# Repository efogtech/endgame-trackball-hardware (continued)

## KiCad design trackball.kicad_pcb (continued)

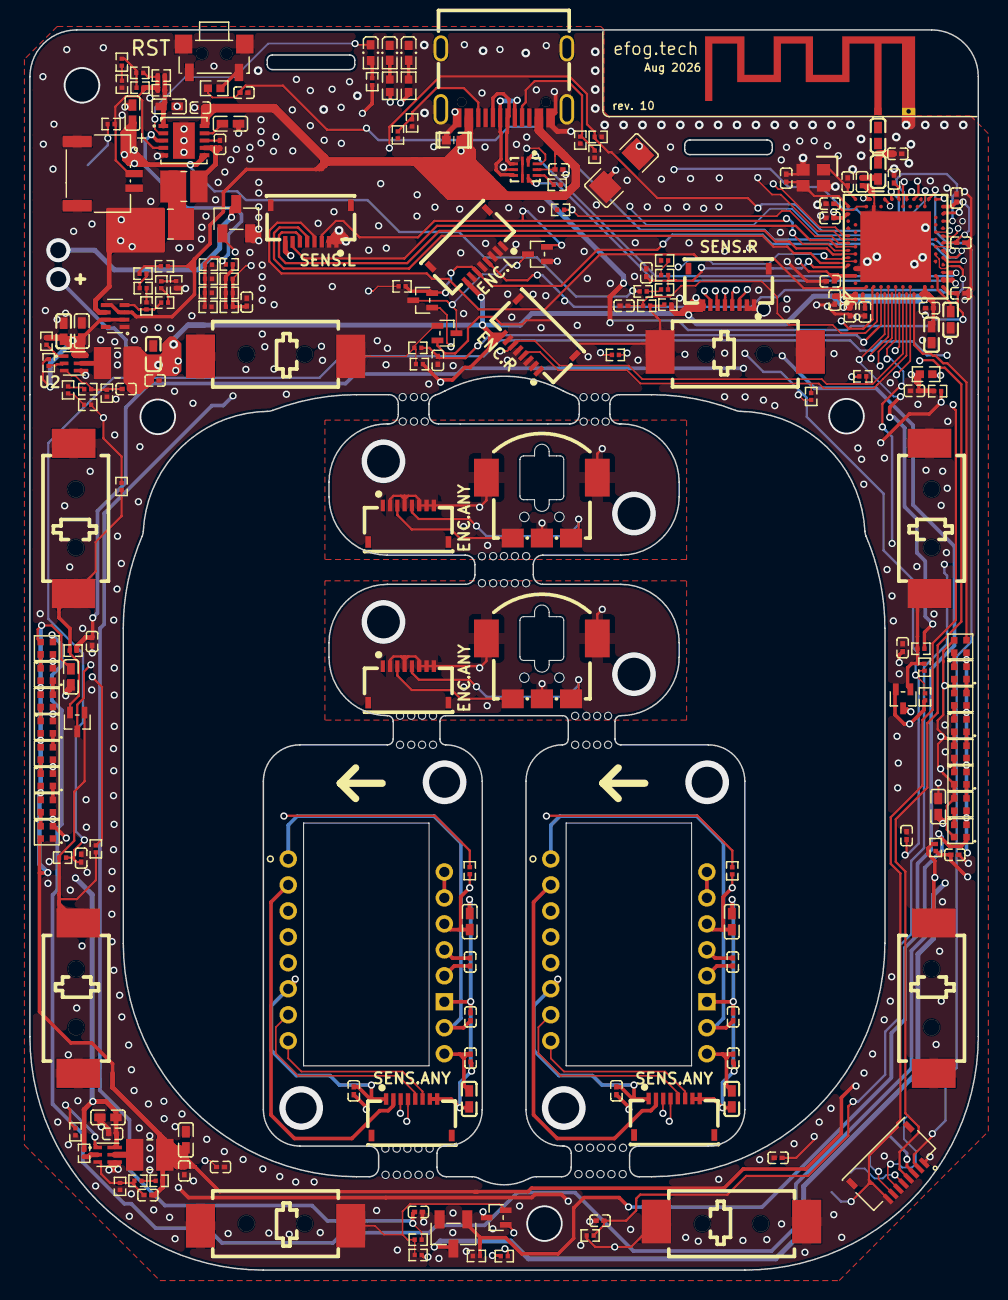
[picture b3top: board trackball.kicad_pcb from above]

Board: 6 copper layers, 65.0 x 85.0 mm, 202 parts (0 on the bottom side), 150 nets.

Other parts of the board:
C30: 0201B821K500NT; C0201
D2, D3, D4, D5, D6, D7: BAS40-06T-7-F; SC-75-3_L1.6-W0.8-P1.00-LS1.6-BR
ENC1#2: EC05E1220401; SW-SMD_EC05E1220401
ENC.ANY, ENC.ANY#2, ENC.L, ENC.R: AFH34-S08FIA-1H; FPC-SMD_8P-P0.50_JS_AFH34-S08FIA-1H
R56: RT0402BRE0750RL; R0402
R57: 0201WMF1002TEE; R0201
SENS.ANY, SENS.ANY#2, SENS.L, SENS.R: AFH34-S08FIA-1H; FPC-SMD_8P-P0.50_JS_AFH34-S08FIA-1H

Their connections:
1V8: ENC.L.8, ENC.R.8, R57.2, SENS.L.8, SENS.R.8; also elsewhere on the board
D_RE1_A: ENC1#2.A, ENC.ANY.3
D_RE1_B: ENC1#2.B, ENC.ANY.5
D_RE1_GND: ENC1#2.4, ENC1#2.5, ENC1#2.C, ENC.ANY.2, ENC.ANY.4, ENC.ANY.6, ENC.ANY.7, ENC.ANY.8
D_RE2_A: ENC.ANY#2.3; also elsewhere on the board
D_RE2_B: ENC.ANY#2.5; also elsewhere on the board
D_RE2_GND: ENC.ANY#2.2, ENC.ANY#2.4, ENC.ANY#2.6, ENC.ANY#2.7, ENC.ANY#2.8; also elsewhere on the board
D_SS1_1V8: SENS.ANY.1; also elsewhere on the board
D_SS1_CLK: SENS.ANY.3; also elsewhere on the board
D_SS1_DIO: SENS.ANY.2; also elsewhere on the board
D_SS1_GND: SENS.ANY.7, SENS.ANY.8; also elsewhere on the board
D_SS1_MTN: SENS.ANY.6; also elsewhere on the board
D_SS1_NCS: SENS.ANY.4; also elsewhere on the board
D_SS1_RST: SENS.ANY.5; also elsewhere on the board
D_SS2_1V8: SENS.ANY#2.1; also elsewhere on the board
D_SS2_CLK: SENS.ANY#2.3; also elsewhere on the board
D_SS2_DIO: SENS.ANY#2.2; also elsewhere on the board
D_SS2_GND: SENS.ANY#2.7, SENS.ANY#2.8; also elsewhere on the board
D_SS2_MTN: SENS.ANY#2.6; also elsewhere on the board
D_SS2_NCS: SENS.ANY#2.4; also elsewhere on the board
D_SS2_RST: SENS.ANY#2.5; also elsewhere on the board
GND: C30.2, ENC.L.1, ENC.L.2, ENC.L.3, ENC.L.5, ENC.L.7, ENC.R.1, ENC.R.2, ENC.R.3, ENC.R.5, ENC.R.7, SENS.L.1, SENS.L.2, SENS.R.1, SENS.R.2, SENS.R.10; also elsewhere on the board
MCU_WAKEUP: C30.1, R56.1, R57.1; also elsewhere on the board
unnamed: D2.3, D3.3, D4.3, D5.3, D6.3, D7.3, R56.2
RE1_A: D7.2, ENC.L.6; also elsewhere on the board
RE1_B: ENC.L.4; also elsewhere on the board
RE2_A: D7.1, ENC.R.6; also elsewhere on the board
RE2_B: ENC.R.4; also elsewhere on the board
SS1_CLK: SENS.L.6; also elsewhere on the board
SS1_DIO: SENS.L.7; also elsewhere on the board
SS1_MTN: D6.2, SENS.L.3; also elsewhere on the board
SS1_NCS: SENS.L.5; also elsewhere on the board
SS1_RST: SENS.L.4; also elsewhere on the board
SS2_CLK: SENS.R.6; also elsewhere on the board
SS2_DIO: SENS.R.7; also elsewhere on the board
SS2_MTN: D6.1, SENS.R.3; also elsewhere on the board
SS2_NCS: SENS.R.5; also elsewhere on the board
SS2_RST: SENS.R.4; also elsewhere on the board
SW1_WK: D2.2; also elsewhere on the board
SW2_WK: D2.1; also elsewhere on the board
SW3_WK: D3.2; also elsewhere on the board
SW4_WK: D3.1; also elsewhere on the board
SW5_WK: D4.2; also elsewhere on the board
SW6_WK: D4.1; also elsewhere on the board
SW7_WK: D5.2; also elsewhere on the board
SW8_WK: D5.1; also elsewhere on the board

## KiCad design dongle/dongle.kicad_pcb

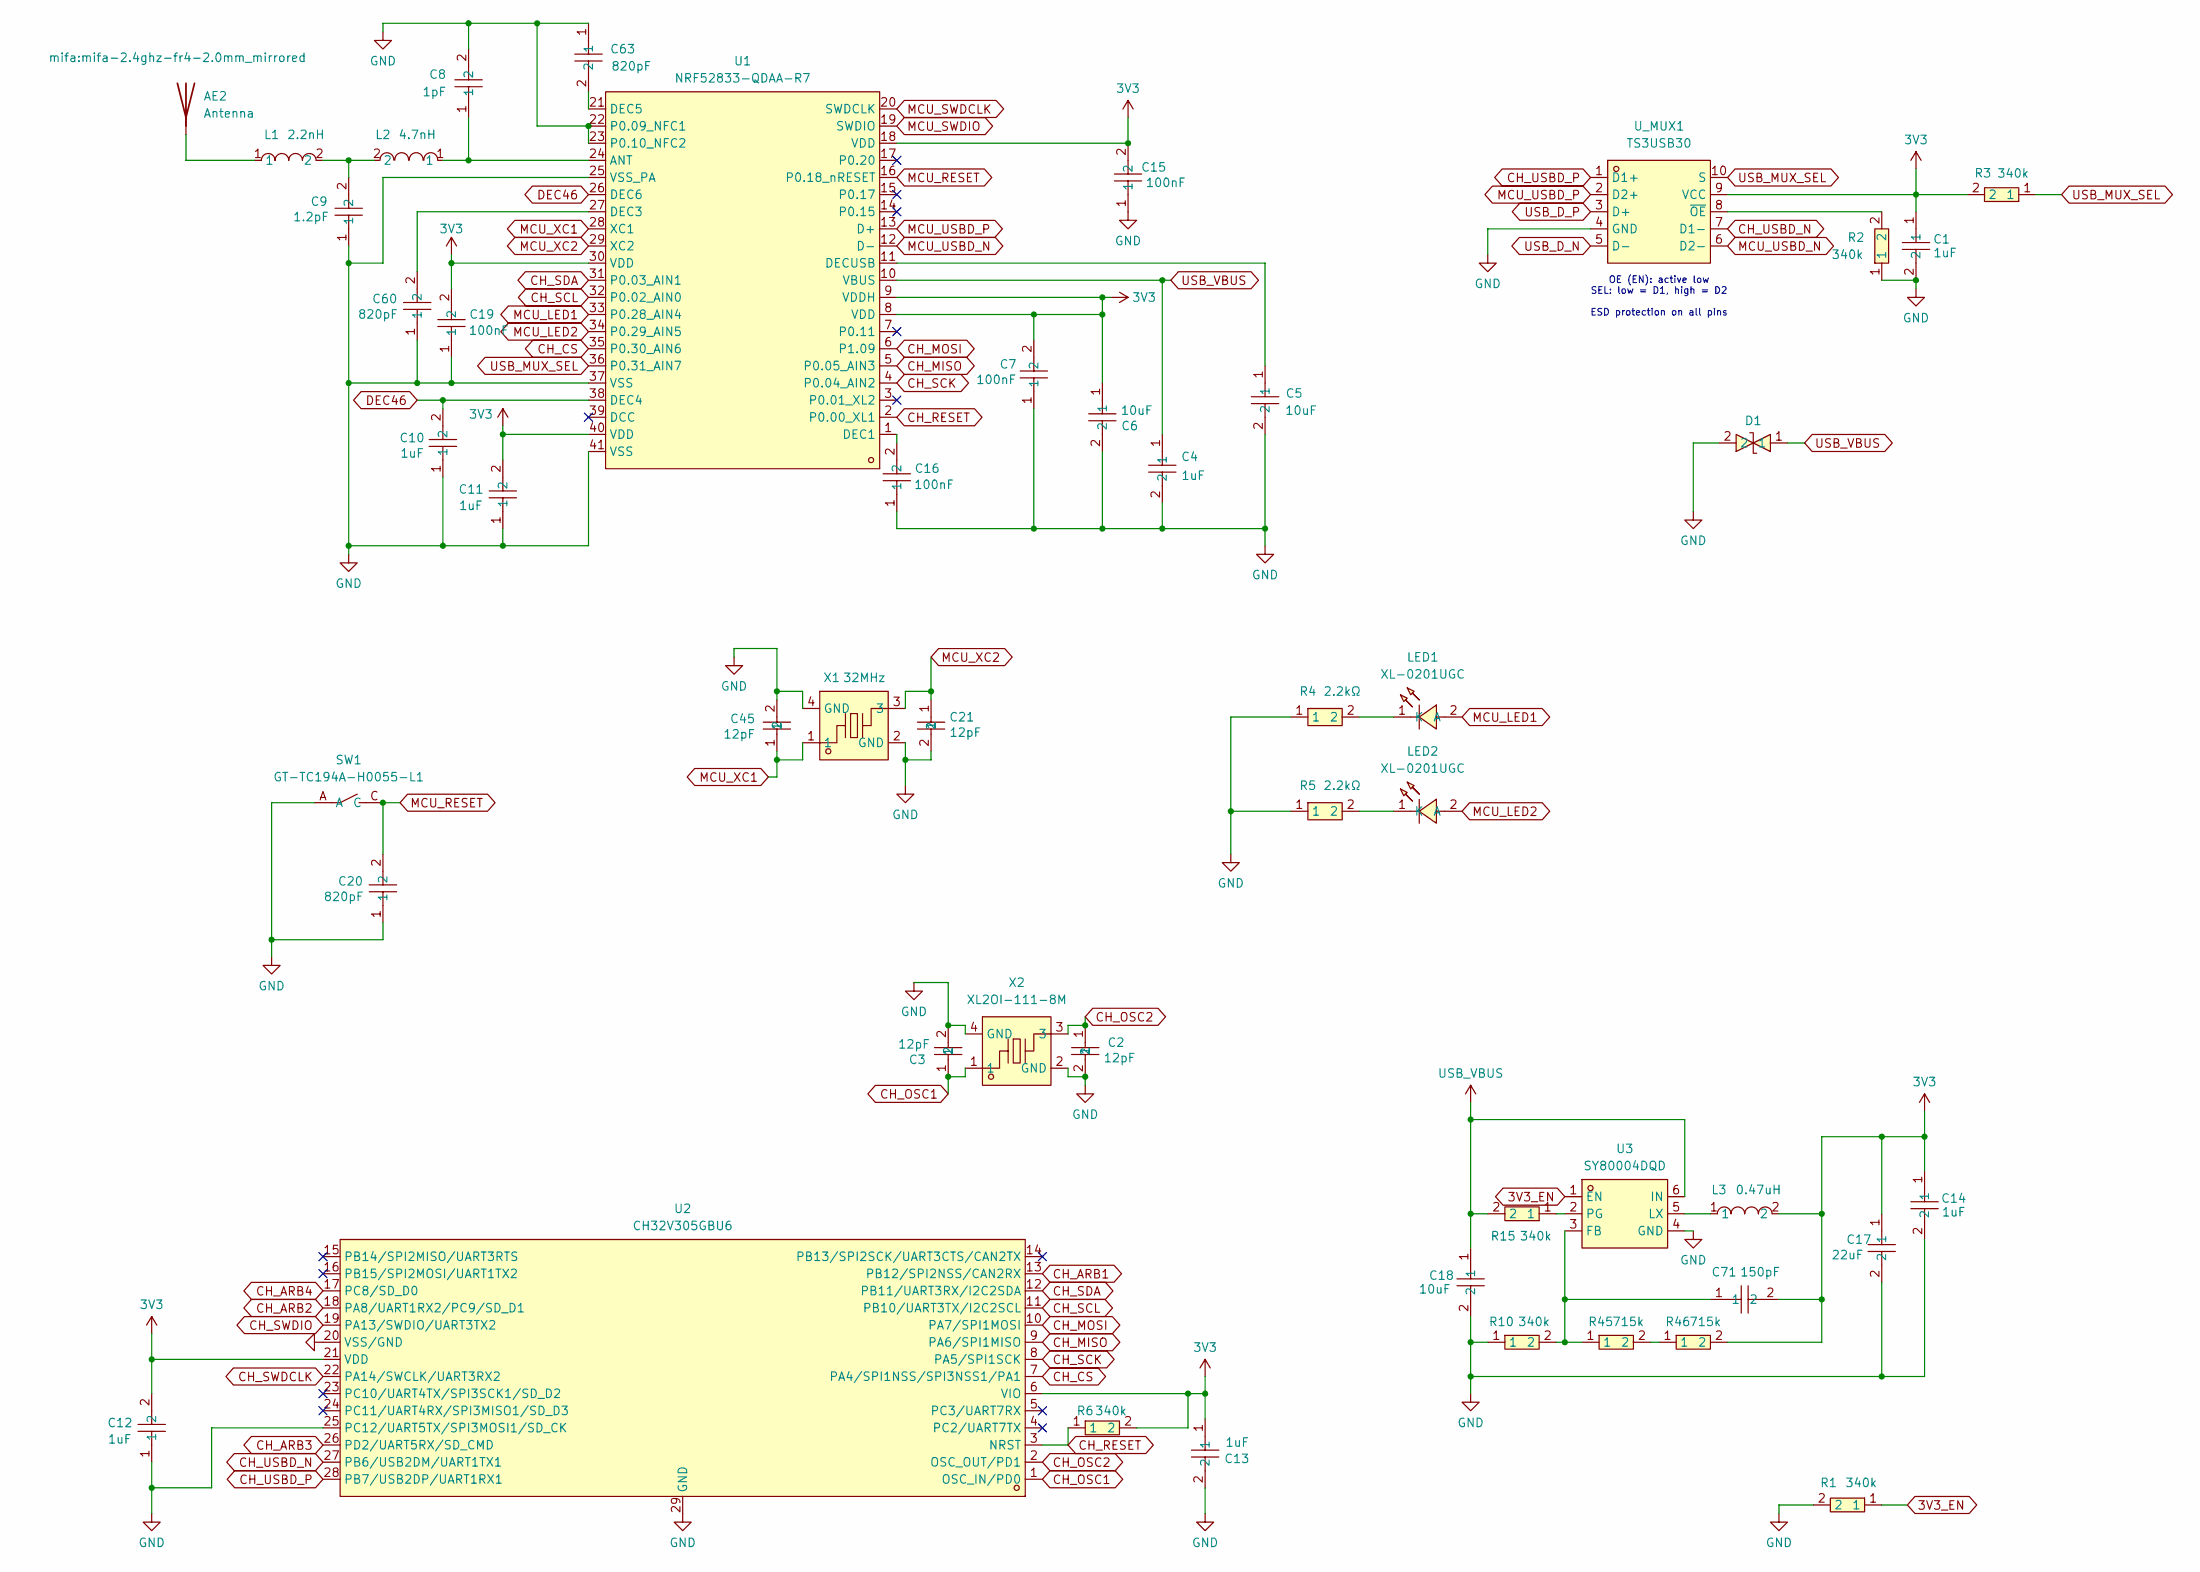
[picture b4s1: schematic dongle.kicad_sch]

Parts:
AE2: Antenna; mifa-2.4ghz-fr4-2.0mm_mirrored
C1, C4, C10, C11, C12, C13, C14: CGA0201X5R105M6R3ET; C0201; LCSC Part C6119749
C2, C3, C21, C45: 0201CG120J500NT; C0201; LCSC Part C50391
C5, C6, C18: CL05A106MP5NUNC_C315248; C0402; LCSC Part C315248
C7, C15, C16, C19: CGA0201X5R104K100ET; C0201; LCSC Part C6119757
C8: 0201CG1R0C250NT; C0201; LCSC Part C301901
C9: CGA0201C0G1R2C500ET; C0201; LCSC Part C22374839
C17: GRM155R60J226ME11D; C0402; LCSC Part C415703
C20, C60, C63: 0201B821K500NT; C0201; LCSC Part C2836759
C71: C0201; LCSC Part C18213206
D1: 0402ESDA-05N; D0402-BI; LCSC Part C316049
L1: LQP03HQ2N2B02D; L0201; LCSC Part C1329438
L2: LQP03HQ4N7H02D; L0201; LCSC Part C237443
L3: FTC252012SR47MBCA; IND-SMD_L2.5-W2.0; LCSC Part C5832368
LED1, LED2: XL-0201UGC; LED-SMD_L0.7-W0.4-RD_GREEN; LCSC Part C3646922
R1, R2, R3, R6, R10, R15: RC-01W103JT; R0201; LCSC Part C320848
R4, R5: 0201WMF2201TEE; R0201; LCSC Part C473508
R45, R46: 715k; R0201; LCSC Part C321023
SW1: GT-TC194A-H0055-L1; SW-SMD_4P-L2.5-W1.6-LS2.9_STI-055A12AX; LCSC Part C41398745
U1: NRF52833-QDAA-R7; QFN-40_L5.0-W5.0-P0.40-TL-EP3.6; LCSC Part C3007767
U2: CH32V305GBU6; QFN-28_L4.0-W4.0-P0.40-BL-EP2.8; LCSC Part C19100608
U3: SY80004DQD; VSON-6_L1.5-W1.5-P0.50-TL; LCSC Part C20617244
U_MUX1: TS3USB30; UQFN-10_L1.8-W1.4-P0.40-TL; LCSC Part C73880
X1: XL7EL89CKI-111YLC-32M; CRYSTAL-SMD_4P-L2.0-W1.6-BL; LCSC Part C2965582
X2: XL2OI-111-8M; CRYSTAL-SMD_4P-L3.2-W2.5-BL; LCSC Part C20617566

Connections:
3V3: C1.1, C6.1, C7.2, C11.2, C12.2, C13.1, C14.1, C15.2, C17.1, C19.2, C71.2, L3.2, R3.2, R6.2, R46.2, U1.8 (VDD), U1.9 (VDDH), U1.18 (VDD), U1.30 (VDD), U1.40 (VDD), U2.6 (VIO), U2.21 (VDD), U_MUX1.9 (VCC)
3V3_EN: R1.1, U3.1 (EN)
CH_ARB1: U2.13 (PB12/SPI2NSS/CAN2RX)
CH_ARB2: U2.18 (PA8/UART1RX2/PC9/SD_D1)
CH_ARB3: U2.26 (PD2/UART5RX/SD_CMD)
CH_ARB4: U2.17 (PC8/SD_D0)
CH_CS: U1.35 (P0.30_AIN6), U2.7 (PA4/SPI1NSS/SPI3NSS1/PA1)
CH_MISO: U1.5 (P0.05_AIN3), U2.9 (PA6/SPI1MISO)
CH_MOSI: U1.6 (P1.09), U2.10 (PA7/SPI1MOSI)
CH_OSC1: C3.1, U2.1 (OSC_IN/PD0), X2.1
CH_OSC2: C2.1, U2.2 (OSC_OUT/PD1), X2.3
CH_RESET: R6.1, U1.2 (P0.00_XL1), U2.3 (NRST)
CH_SCK: U1.4 (P0.04_AIN2), U2.8 (PA5/SPI1SCK)
CH_SCL: U1.32 (P0.02_AIN0), U2.11 (PB10/UART3TX/I2C2SCL)
CH_SDA: U1.31 (P0.03_AIN1), U2.12 (PB11/UART3RX/I2C2SDA)
CH_SWDCLK: U2.22 (PA14/SWCLK/UART3RX2)
CH_SWDIO: U2.19 (PA13/SWDIO/UART3TX2)
CH_USBD_N: U2.27 (PB6/USB2DM/UART1TX1), U_MUX1.7 (D1-)
CH_USBD_P: U2.28 (PB7/USB2DP/UART1RX1), U_MUX1.1 (D1+)
DEC46: C10.2, U1.26 (DEC6), U1.38 (DEC4)
GND: C1.2, C2.2, C3.2, C4.2, C5.2, C6.2, C7.1, C8.2, C9.1, C10.1, C11.1, C12.1, C13.2, C14.2, C15.1, C16.1, C17.2, C18.2, C19.1, C20.1, C21.2, C45.2, C60.1, C63.1, D1.2, R1.2, R2.1, R4.1, R5.1, R10.1, SW1.A, U1.22 (P0.09_NFC1), U1.23 (P0.10_NFC2), U1.25 (VSS_PA), U1.37 (VSS), U1.41 (VSS), U2.20 (VSS/GND), U2.25 (PC12/UART5TX/SPI3MOSI1/SD_CK), U2.29 (GND), U3.4 (GND), U_MUX1.4 (GND), X1.2 (GND), X1.4 (GND), X2.2 (GND), X2.4 (GND)
MCU_LED1: LED1.2 (A), U1.33 (P0.28_AIN4)
MCU_LED2: LED2.2 (A), U1.34 (P0.29_AIN5)
MCU_RESET: C20.2, SW1.C, U1.16 (P0.18_nRESET)
MCU_SWDCLK: U1.20 (SWDCLK)
MCU_SWDIO: U1.19 (SWDIO)
MCU_USBD_N: U1.12 (D-), U_MUX1.6 (D2-)
MCU_USBD_P: U1.13 (D+), U_MUX1.2 (D2+)
MCU_XC1: C45.1, U1.28 (XC1), X1.1
MCU_XC2: C21.1, U1.29 (XC2), X1.3
unnamed: AE2.1 (A), L1.1
unnamed: C9.2, L1.2, L2.2
unnamed: LED1.1 (K), R4.2
unnamed: LED2.1 (K), R5.2
unnamed: R45.2, R46.1
unnamed: C8.1, L2.1, U1.24 (ANT)
unnamed: C16.2, U1.1 (DEC1)
unnamed: C60.2, U1.27 (DEC3)
unnamed: C63.2, U1.21 (DEC5)
unnamed: C5.1, U1.11 (DECUSB)
unnamed: C71.1, R10.2, R45.1, U3.3 (FB)
unnamed: L3.1, U3.5 (LX)
unnamed: R15.1, U3.2 (PG)
unnamed: R2.2, U_MUX1.8 (~OE)
USB_D_N: U_MUX1.5 (D-)
USB_D_P: U_MUX1.3 (D+)
USB_MUX_SEL: R3.1, U1.36 (P0.31_AIN7), U_MUX1.10 (S)
USB_VBUS: C4.1, C18.1, D1.1, R15.2, U1.10 (VBUS), U3.6 (IN)

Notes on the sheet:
OE (EN): active low SEL: low = D1, high = D2 ESD protection on all pins

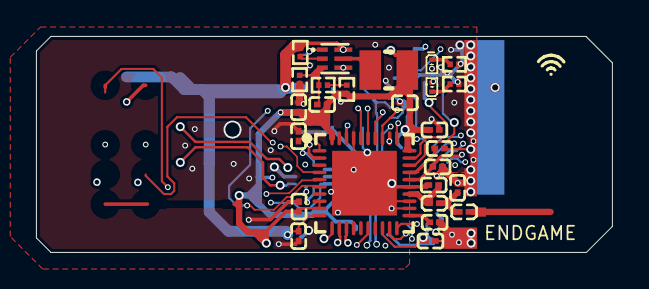
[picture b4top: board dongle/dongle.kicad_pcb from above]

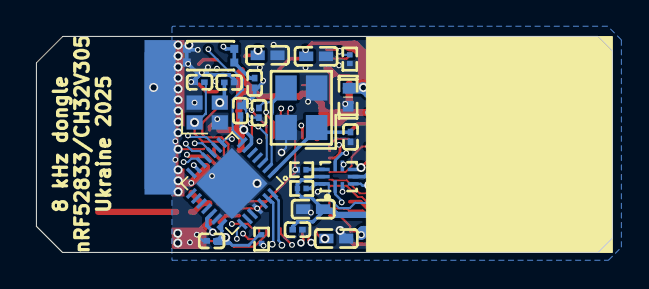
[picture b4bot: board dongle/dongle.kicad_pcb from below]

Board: 6 copper layers, 32.0 x 12.0 mm, 49 parts (22 on the bottom side), 38 nets.

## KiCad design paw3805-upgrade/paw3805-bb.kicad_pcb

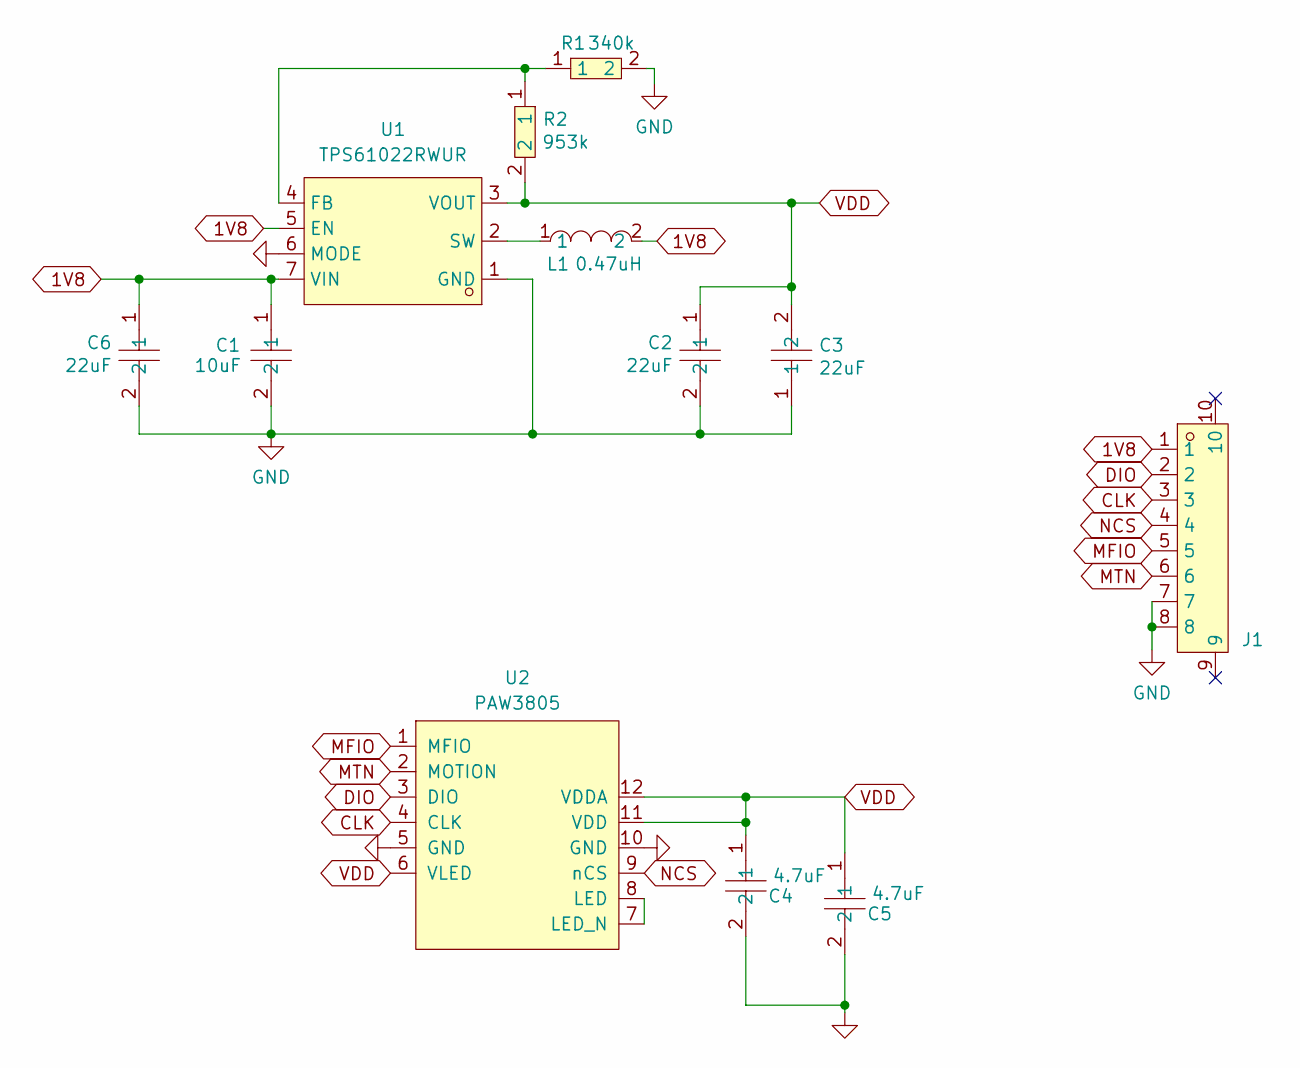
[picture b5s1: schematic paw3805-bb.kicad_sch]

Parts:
C1: CL05A106MP5NUNC_C315248; C0402; LCSC Part C315248
C2, C3, C6: GRM155R60J226ME11D; C0402; LCSC Part C415703
C4, C5: GRM035R60J475ME15D; C0201; LCSC Part C335103
J1: AFH34-S08FIA-1H; FPC-SMD_8P-P0.50_JS_AFH34-S08FIA-1H; LCSC Part C5139822
L1: FTC252012SR47MBCA; IND-SMD_L2.5-W2.0; LCSC Part C5832368
R1: RC-01W103JT; R0201; LCSC Part C320848
R2: RTT019533FTH; R0201; LCSC Part C166079
U1: TPS61022RWUR; VQFN-7_L2.0-W2.0-P0.55-TL_RWU; LCSC Part C915088
U2: PAW3805

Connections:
1V8: C1.1, C6.1, J1.1, L1.2, U1.5 (EN), U1.7 (VIN)
CLK: J1.3, U2.4 (CLK)
DIO: J1.2, U2.3 (DIO)
GND: C1.2, C2.2, C3.1, C4.2, C5.2, C6.2, J1.7, J1.8, R1.2, U1.1 (GND), U1.6 (MODE), U2.5 (GND), U2.10 (GND)
MFIO: J1.5, U2.1 (MFIO)
MTN: J1.6, U2.2 (MOTION)
NCS: J1.4, U2.9 (nCS)
unnamed: R1.1, R2.1, U1.4 (FB)
unnamed: L1.1, U1.2 (SW)
unnamed: U2.7 (LED_N), U2.8 (LED)
VDD: C2.1, C3.2, C4.1, C5.1, R2.2, U1.3 (VOUT), U2.6 (VLED), U2.11 (VDD), U2.12 (VDDA)

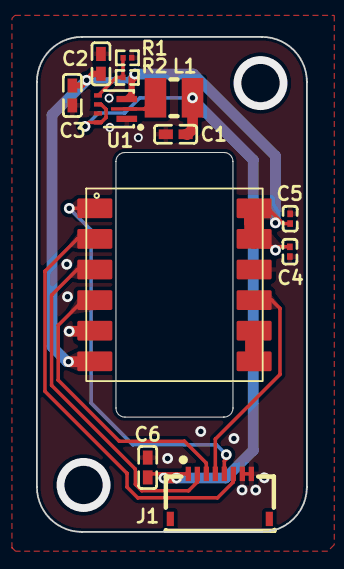
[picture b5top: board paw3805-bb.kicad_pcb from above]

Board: 2 copper layers, 15.0 x 27.5 mm, 12 parts (0 on the bottom side), 11 nets.

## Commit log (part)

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2025-10-07 feat: rev.04 WIP
2025-10-16 feat: rev.04 hardware
2025-10-16 chore: assembly guide improvement
2025-10-16 bugfix: 3d models
2025-10-16 chore: readme
2025-11-12 feat: encoders upgrade; PAW3395 bb; PAW3805 bb
2025-12-15 feat: dongle
2026-01-21 feat: 1k dongle, rev5 hw (wip)
2026-01-22 chore: rev5 hw fixes
2026-03-13 feat: rev7 hardware
2026-03-17 feat: rev7 hardware (final)
2026-03-23 chore: tidy
